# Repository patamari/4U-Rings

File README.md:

# 4U-Rings
4U port of MI Rings, Multimode Resonator

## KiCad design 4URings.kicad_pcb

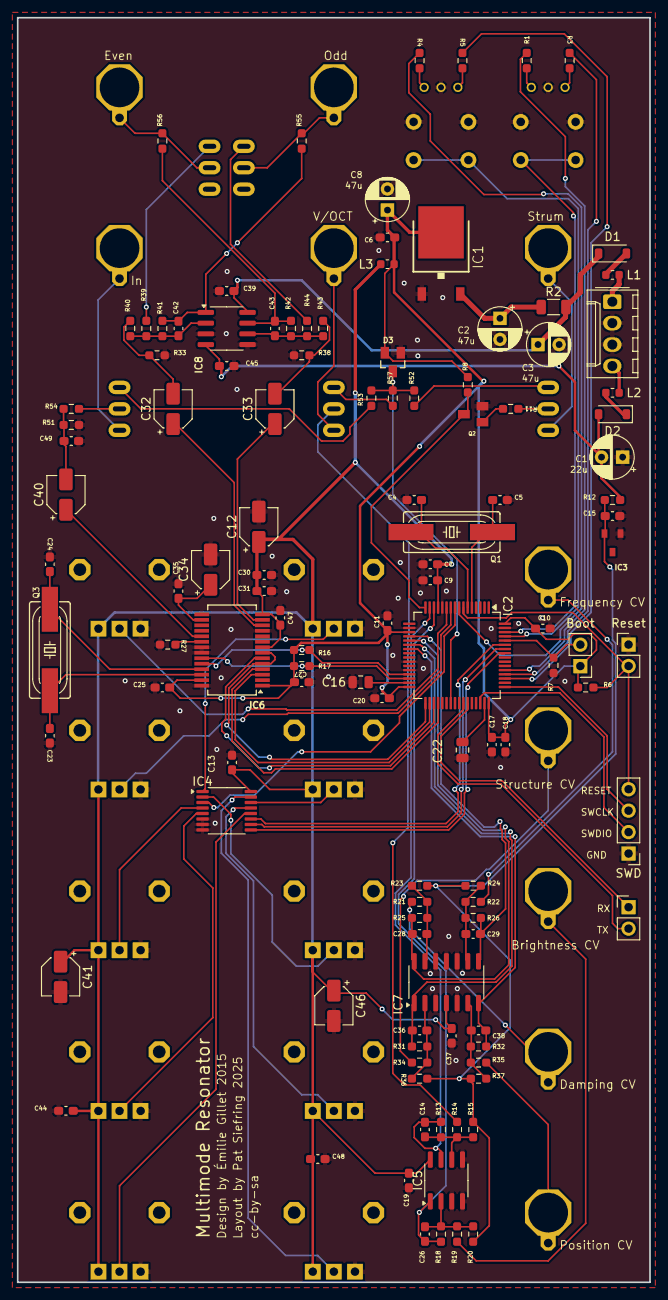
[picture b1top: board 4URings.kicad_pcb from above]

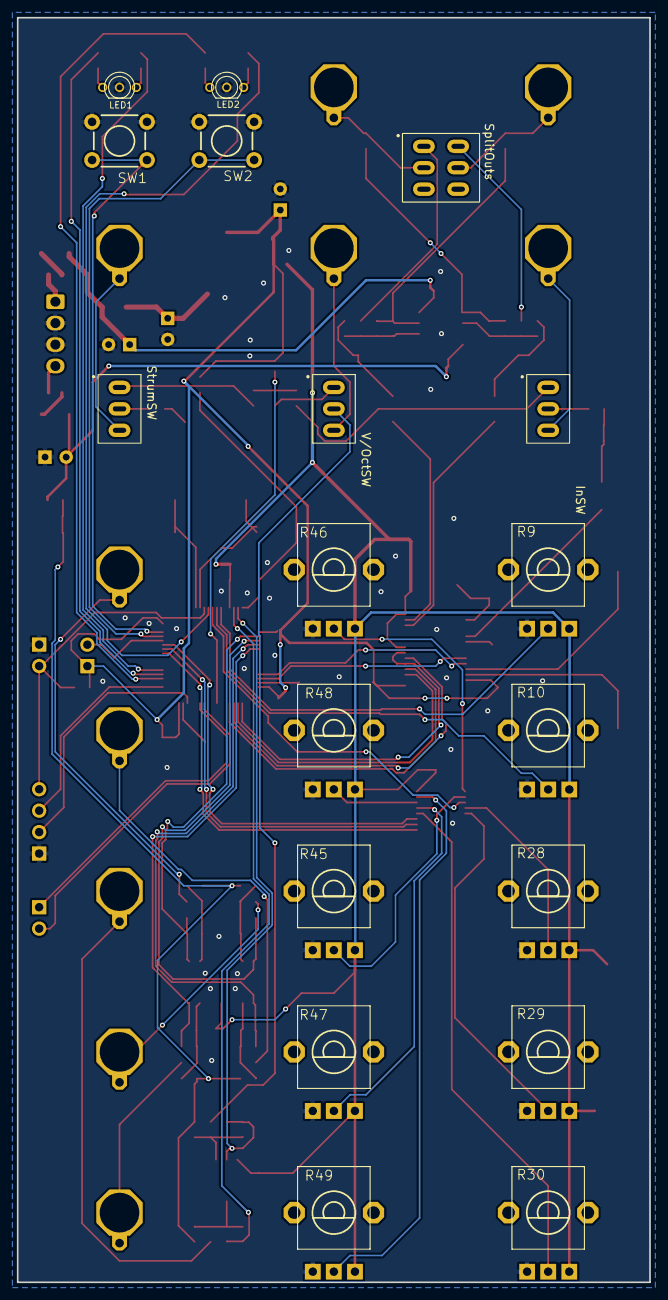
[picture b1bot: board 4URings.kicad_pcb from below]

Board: 2 copper layers, 74.9 x 149.9 mm, 133 parts (18 on the bottom side), 88 nets.

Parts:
Boot: PinHeader_1x02_P2.54mm_Vertical
Boot#2: PinHeader_1x02_P2.54mm_Vertical
C1: 22u; CP_Radial_D5.0mm_P2.50mm
C2, C3, C8: 47u; CP_Radial_D5.0mm_P2.50mm
C4, C5, C23, C24, C42, C43: 18p; C_0603_1608Metric_Pad1.08x0.95mm_HandSolder
C6, C9, C10, C11, C13, C15, C17, C19, C20, C25, C27, C31, C35, C37, C39, C44, C45, C47, C48: 100n; C_0603_1608Metric_Pad1.08x0.95mm_HandSolder
C7, C18, C30: 1u; C_0603_1608Metric_Pad1.08x0.95mm_HandSolder
C12, C32, C33, C34, C40, C41, C46: 10u; CP_Elec_4x5.4
C14, C29: 2.2n; C_0603_1608Metric_Pad1.08x0.95mm_HandSolder
C16, C22: 2.2u; C_0805_2012Metric
C26, C28, C36, C38: 10n; C_0603_1608Metric_Pad1.08x0.95mm_HandSolder
C49: 220p; C_0603_1608Metric_Pad1.08x0.95mm_HandSolder
D1, D2: 1N5819HW; D_SOD-123
D3: BAT54S; SOT23
IC1: LM1117-3.3; TO252
IC2: STM32F405RGT6; TQFP-64_10x10mm_P0.5mm
IC3: LM4040B10; DBZ_R-PDSO-G3
IC4: 4051PW; TSSOP-16_4.4x5mm_P0.65mm
IC5: MCP6002; SOIC-8_3.9x4.9mm_P1.27mm
IC6: WM8731; SSOP-28_5.3x10.2mm_P0.65mm
IC7: MCP6004; SOIC-14_3.9x8.7mm_P1.27mm
IC8: TL072; SOIC-8_3.9x4.9mm_P1.27mm
InSW: SubMiniSPDT2.54mm; SubMiniSwitch2.54mm
L1, L2, L3: L_0603_1608Metric
LED1, LED2: WP115VEGW; LED-BICOLOR-THROUGHHOLE
Q1: 8MHz; HC49UP
Q2: MMBT3904; SOT23-BEC
Q3: 12.288MHz; HC49UP
R1, R3, R4, R5: 180; R_0603_1608Metric_Pad0.98x0.95mm_HandSolder
R2: 4.7; R_1206_3216Metric
R6, R7, R8: 10k; R_0603_1608Metric_Pad0.98x0.95mm_HandSolder
R9, R10, R28, R29, R30, R45, R46, R47, R48, R49: 10kB; ALPS_POT_VERTICAL_PS
R11, R14, R19, R21, R22, R34, R35, R52: 100k; R_0603_1608Metric_Pad0.98x0.95mm_HandSolder
R12, R16, R17: 2.2k; R_0603_1608Metric_Pad0.98x0.95mm_HandSolder
R13, R33, R38, R39, R41, R42, R44: 47k; R_0603_1608Metric_Pad0.98x0.95mm_HandSolder
R15: 180k; R_0603_1608Metric_Pad0.98x0.95mm_HandSolder
R18, R25, R26, R31, R32: 20k; R_0603_1608Metric_Pad0.98x0.95mm_HandSolder
R20, R23, R24, R36, R37: 120k; R_0603_1608Metric_Pad0.98x0.95mm_HandSolder
R27, R54: 36k; R_0603_1608Metric_Pad0.98x0.95mm_HandSolder
R40, R43, R51: 6.8k; R_0603_1608Metric_Pad0.98x0.95mm_HandSolder
R53: 1M; R_0603_1608Metric_Pad0.98x0.95mm_HandSolder
R55, R56: 1.0k; R_0603_1608Metric_Pad0.98x0.95mm_HandSolder
R57: 470k; R_0603_1608Metric_Pad0.98x0.95mm_HandSolder
Reset: PinHeader_1x02_P2.54mm_Vertical
SW1, SW2: TACTILE-PTH
SWD: PinHeader_1x04_P2.54mm_Vertical
SplitOuts: SubMiniDPDT2.54mm; SubMiniSwitchDPDT2.54mm
StrumSW: SubMiniSPDT2.54mm; SubMiniSwitch2.54mm
V/OctSW: SubMiniSPDT2.54mm; SubMiniSwitch2.54mm

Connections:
+3V3: Boot#2.1, C6.1, C8.1, C10.1, C11.1, C17.1, C18.1, C20.1, C25.1, C27.1, D3.2, IC1.3, IC2.19, IC2.32, IC2.48, IC2.64, IC6.1, IC6.27, L3.1, R6.2, R8.2, R16.2, R17.2
+3V3_A: C7.1, C9.1, C12.1, C13.1, C19.1, C30.1, C31.1, C37.1, C41.1, C44.1, C46.1, C47.1, C48.1, IC2.13, IC4.16, IC5.8, IC6.8, IC6.14, IC7.4, L3.2, R9.P$1, R10.P$1, R28.P$1, R29.P$1, R30.P$1, R45.P$1, R46.P$1, R47.P$1, R48.P$1, R49.P$1
AREF_-10: C15.1, IC3.2, R12.2, R15.2, R20.2, R23.2, R24.2, R36.2, R37.2
AUX_OUT: C33.1, IC6.13
BOOT_FLASH: Boot#2.2, IC2.60, R7.2
BRIGHTNESS_ATT: IC4.2, R45.P$2
BRIGHTNESS_CV: C26.2, IC2.14, IC5.1, R18.1
BRIGHTNESS_POT: IC4.4, R28.P$2
CV_NORMALIZATION: R57.2, V/OctSW.1
DAMP_ATT: IC4.13, R47.P$2
DAMP_CV: C28.2, IC2.21, IC7.14, R25.1
DAMP_POT: IC4.5, R29.P$2
FM_CV: C29.2, IC2.20, IC7.8, R26.1
FREQUENCY_ATT: IC4.1, R46.P$2
FREQUENCY_POT: IC2.11, R9.P$2
GEOMETRY_ATT: IC4.14, R48.P$2
GEOMETRY_CV: C36.2, IC2.22, IC7.1, R31.1
GEOMETRY_POT: IC2.10, R10.P$2
GND: C1.1, C2.2, C3.2, C4.1, C5.1, C6.2, C7.2, C8.2, C9.2, C10.2, C11.2, C12.2, C13.2, C15.2, C16.2, C17.2, C18.2, C19.2, C20.2, C22.2, C23.1, C24.1, C25.2, C27.2, C30.2, C31.2, C34.2, C35.2, C37.2, C39.2, C41.2, C44.2, C45.1, C46.2, C47.2, C48.2, C49.2, D3.1, IC1.1, IC2.12, IC2.18, IC2.26, IC2.28, IC2.63, IC3.1, IC4.6, IC4.7, IC4.8, IC5.3, IC5.4, IC5.5, IC6.11, IC6.15, IC6.21, IC6.22, IC6.28, IC7.3, IC7.5, IC7.10, IC7.11, IC7.12, IC8.3, IC8.5, LED1.2, LED2.2, Q2.E, R7.1, R9.P$3, R10.P$3, R27.2, R28.P$3, R29.P$3, R30.P$3, R33.1, R38.1, R45.P$3, R46.P$3, R47.P$3, R48.P$3, R49.P$3, R51.1, Reset.1, SW1.1, SW1.2, SW2.1, SW2.2, SWD.1
I2C_SCL: IC2.29, IC6.24, R16.1
I2C_SDA: IC2.30, IC6.23, R17.1
I2S_LRCK: IC2.33, IC6.5, IC6.7
I2S_SCK: IC2.34, IC6.3
I2S_SIN: IC2.35, IC6.6
I2S_SOUT: IC2.36, IC6.4
IN_1: IC6.20, R27.1
IN_2: C40.1, IC6.19
JTCK: IC2.49, SWD.3
JTMS: IC2.46, SWD.2
MAIN_OUT: C32.1, IC6.12
MUXED_POTS: IC2.9, IC4.3
MUX_ADDR_0: IC2.59, IC4.11
MUX_ADDR_1: IC2.58, IC4.10
MUX_ADDR_2: IC2.57, IC4.9
unnamed: C26.1, IC5.2, R18.2, R19.1, R20.1
unnamed: R14.2, V/OctSW.2
unnamed: C29.1, IC7.9, R22.1, R24.1, R26.2
unnamed: C5.2, IC2.5, Q1.2
unnamed: C4.2, IC2.6, Q1.1
unnamed: R11.1, StrumSW.2
unnamed: C28.1, IC7.13, R21.1, R23.1, R25.2
unnamed: LED1.3, R1.2
unnamed: C22.1, IC2.47
unnamed: C14.1, IC5.6, R13.2, R14.1, R15.1
unnamed: C36.1, IC7.2, R31.2, R34.1, R36.1
unnamed: C2.1, IC1.2, R2.1
unnamed: C34.1, C35.1, IC6.16
unnamed: C40.2, C49.1, R51.2, R54.1
unnamed: C16.1, IC2.31
unnamed: R52.2, StrumSW.1
unnamed: InSW.2, R54.2
unnamed: LED1.1, R3.2
unnamed: C33.2, R38.2, R43.2
unnamed: D1.2, L1.1
unnamed: C43.1, IC8.6, R42.2, R43.1, R44.1
unnamed: LED2.3, R4.2
unnamed: C43.2, IC8.7, R42.1, R56.2
unnamed: R56.1, SplitOuts.2
unnamed: C38.1, IC7.6, R32.2, R35.1, R37.1
unnamed: C32.2, R33.2, R40.2
unnamed: C42.1, IC8.2, R39.1, R40.1, R41.2
unnamed: C42.2, IC8.1, R41.1, R55.2
unnamed: R55.1, SplitOuts.5
unnamed: LED2.1, R5.2
unnamed: D2.1, L2.1
unnamed: IC2.52, R3.1
unnamed: InSW.1, R53.2
unnamed: IC2.8, R4.1
unnamed: C24.2, IC6.25, Q3.2
unnamed: C23.2, IC6.26, Q3.1
unnamed: IC2.53, R1.1
unnamed: IC2.51, R5.1
unnamed: R39.2, SplitOuts.1
unnamed: R44.2, SplitOuts.4
unnamed: Q2.B, R11.2
NORMALIZATION_PROBE: D3.3, IC2.39, R52.1, R53.1, R57.1
POSITION_ATT: IC4.15, R49.P$2
POSITION_CV: C38.2, IC2.23, IC7.7, R32.1
POSITION_POT: IC4.12, R30.P$2
RESET: IC2.7, R6.1, Reset.2, SWD.4
RX: Boot.1, IC2.43
STRUM: IC2.16, Q2.C, R8.1
SW_MODE: IC2.61, SW2.3, SW2.4
SW_POLYPHONY: IC2.62, SW1.3, SW1.4
TX: Boot.2, IC2.42
VCC: C3.1, C39.1, D1.1, IC8.8, R2.2
VEE: C1.2, C45.2, D2.2, IC8.4, R12.1
V_OCT_CV: C14.2, IC2.15, IC5.7, R13.1

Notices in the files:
4URings.kicad_pcb:
cc-by-sa
